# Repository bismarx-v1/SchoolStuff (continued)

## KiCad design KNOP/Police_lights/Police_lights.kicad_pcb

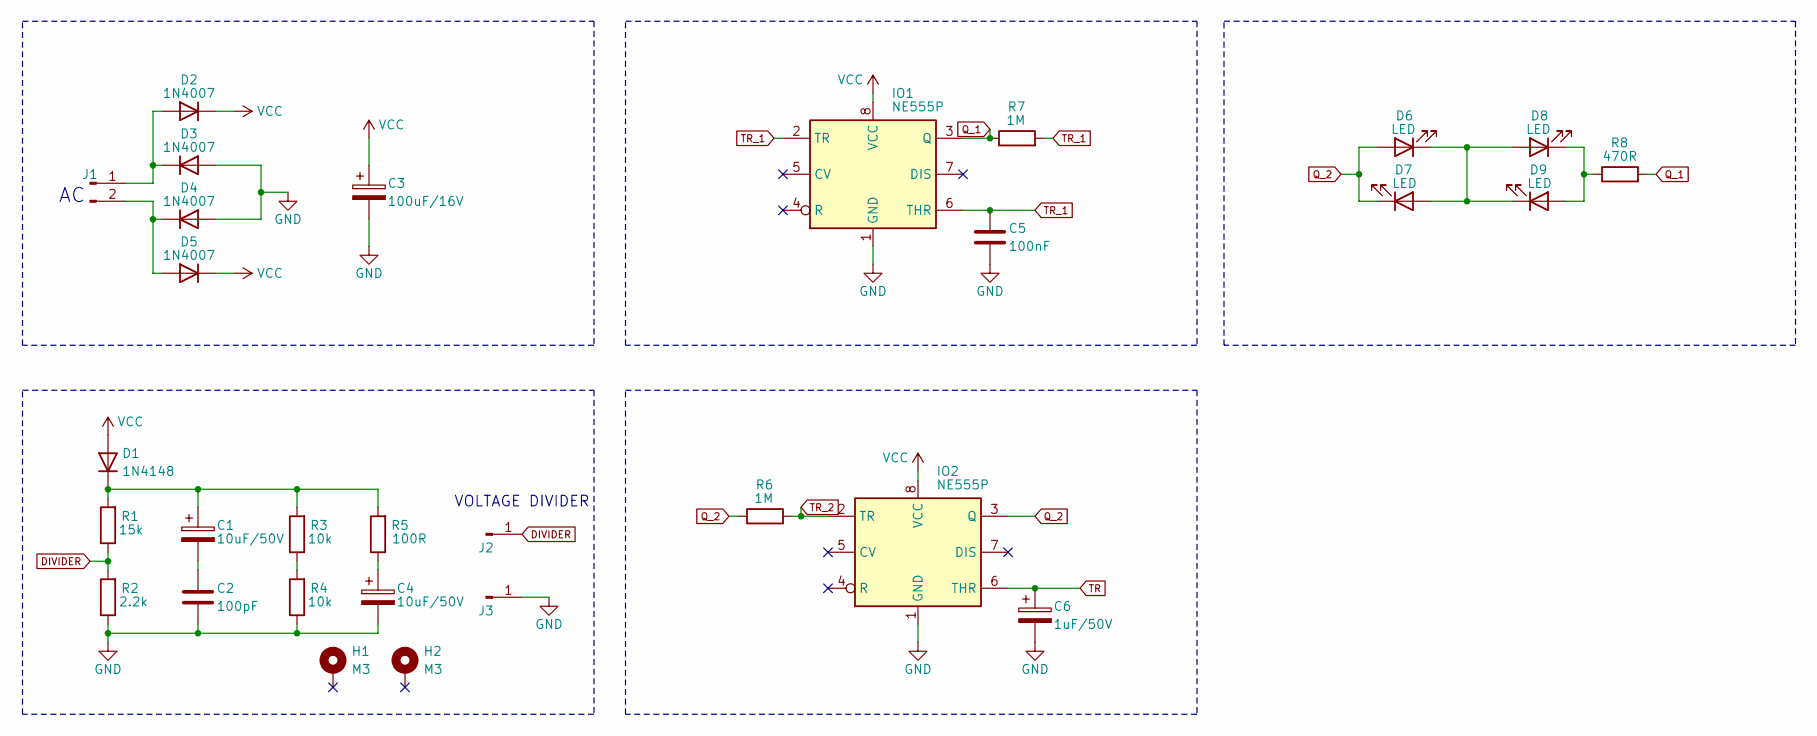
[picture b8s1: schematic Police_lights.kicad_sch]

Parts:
C1, C4: 10uF/50V; CP_Radial_D6.3mm_P2.50mm
C2: 100pF; C_Disc_D6.0mm_W2.5mm_P5.00mm
C3: 100uF/16V; CP_Radial_D6.3mm_P2.50mm
C5: 100nF; C_Disc_D6.0mm_W2.5mm_P5.00mm
C6: 1uF/50V; CP_Radial_D6.3mm_P2.50mm
D1: 1N4148; D_DO-35_SOD27_P7.62mm_Horizontal
D2, D3, D4, D5: 1N4007; D_DO-41_SOD81_P10.16mm_Horizontal
D6, D7, D8, D9: LED; LED_D5.0mm_Clear
H1, H2: M3; MountingHole_3.2mm_M3_DIN965_Pad_TopBottom
IO1, IO2: NE555P; DIP-8_W7.62mm
J1: Conn_01x02_Pin; PinHeader_1x02_P2.54mm_Vertical
J2, J3: DC; PinHeader_1x01_P2.54mm_Vertical
R1: 15k; R_Axial_DIN0207_L6.3mm_D2.5mm_P10.16mm_Horizontal
R2: 2.2k; R_Axial_DIN0207_L6.3mm_D2.5mm_P10.16mm_Horizontal
R3, R4: 10k; R_Axial_DIN0207_L6.3mm_D2.5mm_P10.16mm_Horizontal
R5: 100R; R_Axial_DIN0207_L6.3mm_D2.5mm_P10.16mm_Horizontal
R6, R7: 1M; R_Axial_DIN0207_L6.3mm_D2.5mm_P10.16mm_Horizontal
R8: 470R; R_Axial_DIN0207_L6.3mm_D2.5mm_P10.16mm_Horizontal

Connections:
DIVIDER: J2.1, R1.1, R2.2
GND: C2.2, C3.2, C4.2, C5.2, C6.2, D3.2 (A), D4.2 (A), IO1.1 (GND), IO2.1 (GND), J3.1, R2.1, R4.1; also elsewhere on the board
unnamed: C1.2, C2.1
unnamed: C4.1, R5.1
unnamed: C1.1, D1.1 (K), R1.2, R3.2, R5.2
unnamed: D2.2 (A), D3.1 (K), J1.1
unnamed: D4.1 (K), D5.2 (A), J1.2
unnamed: D6.1 (K), D7.2 (A), D8.2 (A), D9.1 (K)
unnamed: D8.1 (K), D9.2 (A), R8.1
unnamed: R3.1, R4.2
Q_1: IO1.3 (Q), R7.1, R8.2; also elsewhere on the board
Q_2: D6.2 (A), D7.1 (K), IO2.3 (Q), R6.1; also elsewhere on the board
TR: C6.1, IO2.6 (THR); also elsewhere on the board
TR_1: C5.1, IO1.2 (TR), IO1.6 (THR), R7.2; also elsewhere on the board
TR_2: IO2.2 (TR), R6.2; also elsewhere on the board
VCC: C3.1, D1.2 (A), D2.1 (K), D5.1 (K), IO1.8 (VCC), IO2.8 (VCC); also elsewhere on the board

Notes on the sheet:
VOLTAGE DIVIDER

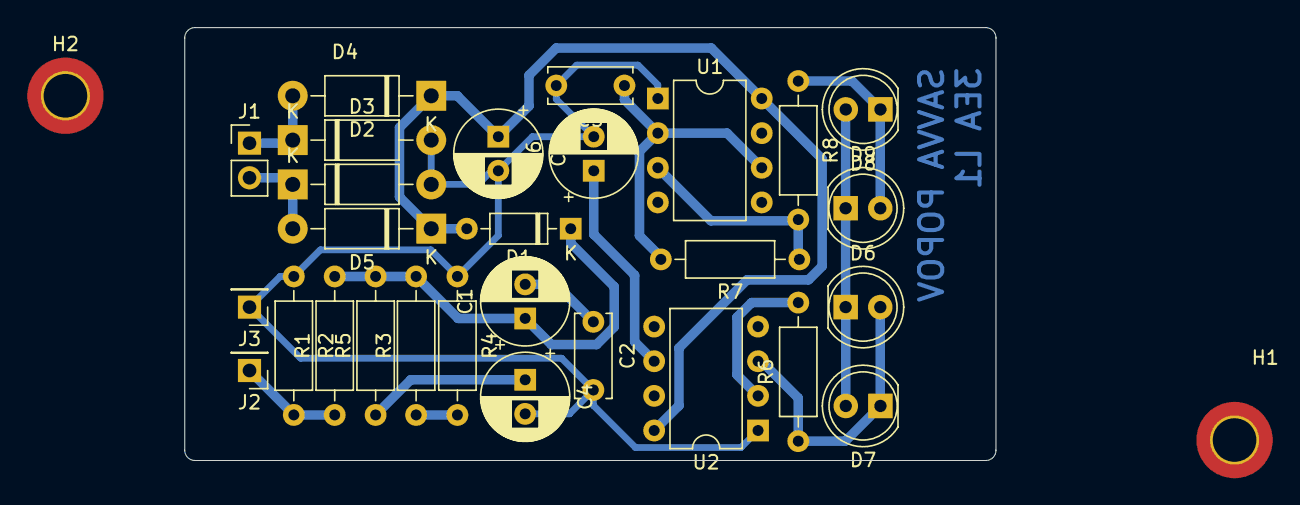
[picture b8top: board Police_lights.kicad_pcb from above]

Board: 2 copper layers, 59.5 x 31.8 mm, 30 parts (0 on the bottom side), 16 nets.

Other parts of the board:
U1, U2: NE555P; DIP-8_W7.62mm

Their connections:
GND: U1.1 (GND), U2.1 (GND); also elsewhere on the board
Q_1: U1.3 (Q); also elsewhere on the board
Q_2: U2.3 (Q); also elsewhere on the board
TR: U2.6 (THR); also elsewhere on the board
TR_1: U1.2 (TR), U1.6 (THR); also elsewhere on the board
TR_2: U2.2 (TR); also elsewhere on the board
VCC: U1.8 (VCC), U2.8 (VCC); also elsewhere on the board

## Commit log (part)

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2023-12-08 Start of Robotic Day.md
2024-06-06 DWG 16
2024-06-07 Start of EI
2024-06-09 Jakub Balcar je cool clovek
2024-06-09 sedl;'fksefkd
2024-06-10 Installation update - finished
2024-06-11 Rozvadec update
2024-06-11 start again form the start and draw it urself
2024-06-12 R update
2024-06-12 Rozvadec done
2024-06-13 R update 2
2024-06-13 Final R update
2024-06-13 Excel start of
2024-09-13 ARDUINO COMMIT
2024-09-13 arduino
2024-09-13 lesson 1
2024-09-13 Busek code import
2024-09-13 arduino fix
2024-09-13 Blink
2024-09-17 IR Remote start
2024-09-17 Task 01, pcb done
    dont forget about gitignore
2024-09-17 PCB update
2024-09-17 job stuff
2024-09-17 will add gitignore later
2024-09-19 v2 fuckamagog thigamajig
2024-09-19 asdasd
2024-09-20 nothing
2024-10-02 test n125 - KiCAD
2024-10-04 busek prog
2024-10-08 oixdjvoisd
2024-10-15 Knops IR emitter schematic
2024-10-16 0 update
2024-10-26 some electrical installation bs
2024-11-08 folder reorder - programming
2024-11-15 folder changes
2024-11-28 rgb led prog
2024-11-29 test3
2024-12-18 knops schematic chnages
2025-01-09 start of dcouple
2025-01-10 Optocoupler update
2025-01-11 will be removed
2025-01-11 deletion
2025-01-22 plotting + pcb
2025-01-28 creation of statistics excel file
2025-01-28 added Natanis excel, updated my own file
2025-02-03 Math-statistics
2025-02-04 parsinset
2025-02-06 statistics update
2025-02-09 Nat helps with code - bareBones
2025-02-16 Busek school stuff
2025-02-25 Hodanova task - done
2025-03-05 no uopdate
2025-03-06 police lights plot
2025-03-24 lf lap trimer
2025-03-25 Footprint update
2025-03-25 timer gate code done
    I unfortunately forgot how it works. It's also untested.
2025-03-25 button changes
2025-03-25 LF LAP TIMER
2025-03-27 final version
2025-03-27 code-zip
2025-03-28 Lap timer plots
2025-03-28 asdas
2025-03-28 there is a bug
2025-03-28 Bug fixed!?
    After thinking for a bit we came to the conclusion that the input isn't debounced enough. This should give a time of 1s to clear the gate before being able to trigger again.
    Github on mobile ftw :3.
2025-03-29 done?
2025-03-29 I left debug mode on >w<
2025-03-30 3d step file
2025-03-31 pdf plot
2025-04-01 something
2025-04-01 this one is working
2025-04-30 IR Remote updates
    IR RX and TX PCB updates
2025-05-15 programminf lessons
2025-05-15 PCB updates
2025-06-09 cahrlie's sd card
    without the large images qwq
2025-06-10 charlies sd
2025-06-10 pcb updates
    (no update)
2025-07-07 charlie sd card
2025-07-12 sd card
2025-08-12 sd card final edit
2025-08-12 order placed
2025-10-03 charlie SD update
2025-12-09 folder cleanup
2025-12-18 jhbhj
2026-01-25 rose pcb
2026-01-28 plotting
2026-03-02 rose update
2026-03-02 kicadedit
2026-03-04 rose asm update
2026-03-04 knop guiater update
2026-03-10 knop guitar
